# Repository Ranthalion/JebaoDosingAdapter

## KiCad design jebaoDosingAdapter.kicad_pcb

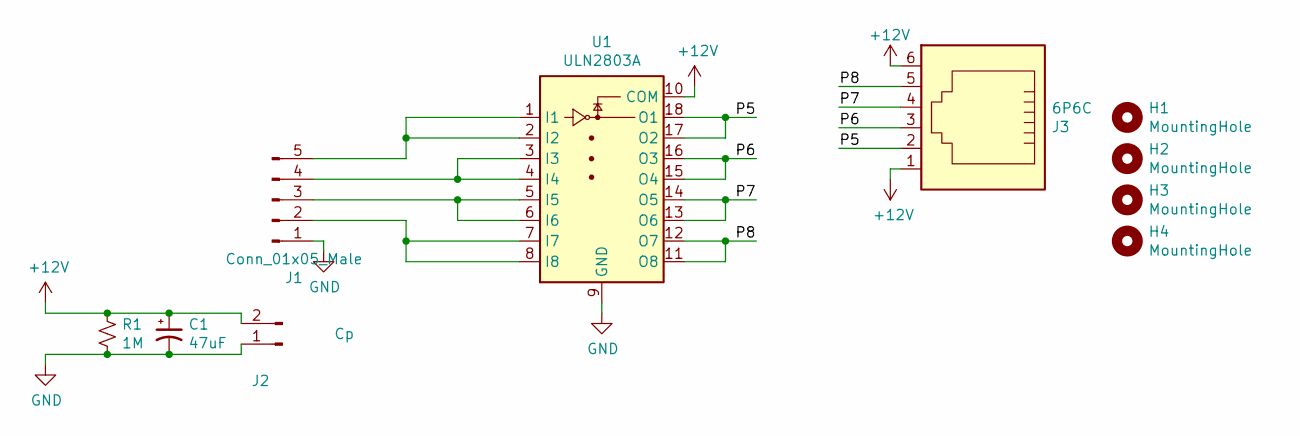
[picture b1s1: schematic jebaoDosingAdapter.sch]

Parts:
C1: 47uF; CP_Radial_D6.3mm_P2.50mm
H1, H2, H3, H4: MountingHole; MountingHole_3.2mm_M3
J1: Conn_01x05_Male; JST_XH_B05B-XH-A_1x05_P2.50mm_Vertical
J2: Cp; JST_XH_B02B-XH-A_1x02_P2.50mm_Vertical
J3: 6P6C; RJ11
R1: 1M; 0603
U1: ULN2803A; SOIC-18W_7.5x11.6mm_P1.27mm

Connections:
+12V: C1.1, J2.2, J3.1, J3.6, R1.1, U1.10 (COM)
/P5: J3.2, U1.17 (O2), U1.18 (O1)
/P6: J3.3, U1.15 (O4), U1.16 (O3)
/P7: J3.4, U1.13 (O6), U1.14 (O5)
/P8: J3.5, U1.11 (O8), U1.12 (O7)
GND: C1.2, J1.1, J2.1, R1.2, U1.9 (GND)
unnamed: J1.2, U1.7 (I7), U1.8 (I8)
unnamed: J1.3, U1.5 (I5), U1.6 (I6)
unnamed: J1.4, U1.3 (I3), U1.4 (I4)
unnamed: J1.5, U1.1 (I1), U1.2 (I2)

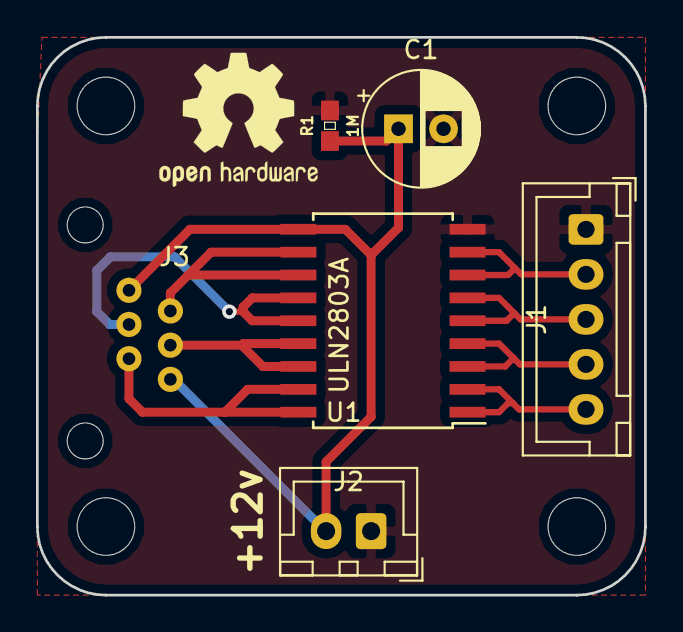
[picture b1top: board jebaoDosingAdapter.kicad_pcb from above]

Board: 2 copper layers, 33.8 x 31.0 mm, 10 parts (0 on the bottom side), 10 nets.

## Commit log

2020-02-06 Add images and updated gerbers
2020-02-29 Double up driver and document
